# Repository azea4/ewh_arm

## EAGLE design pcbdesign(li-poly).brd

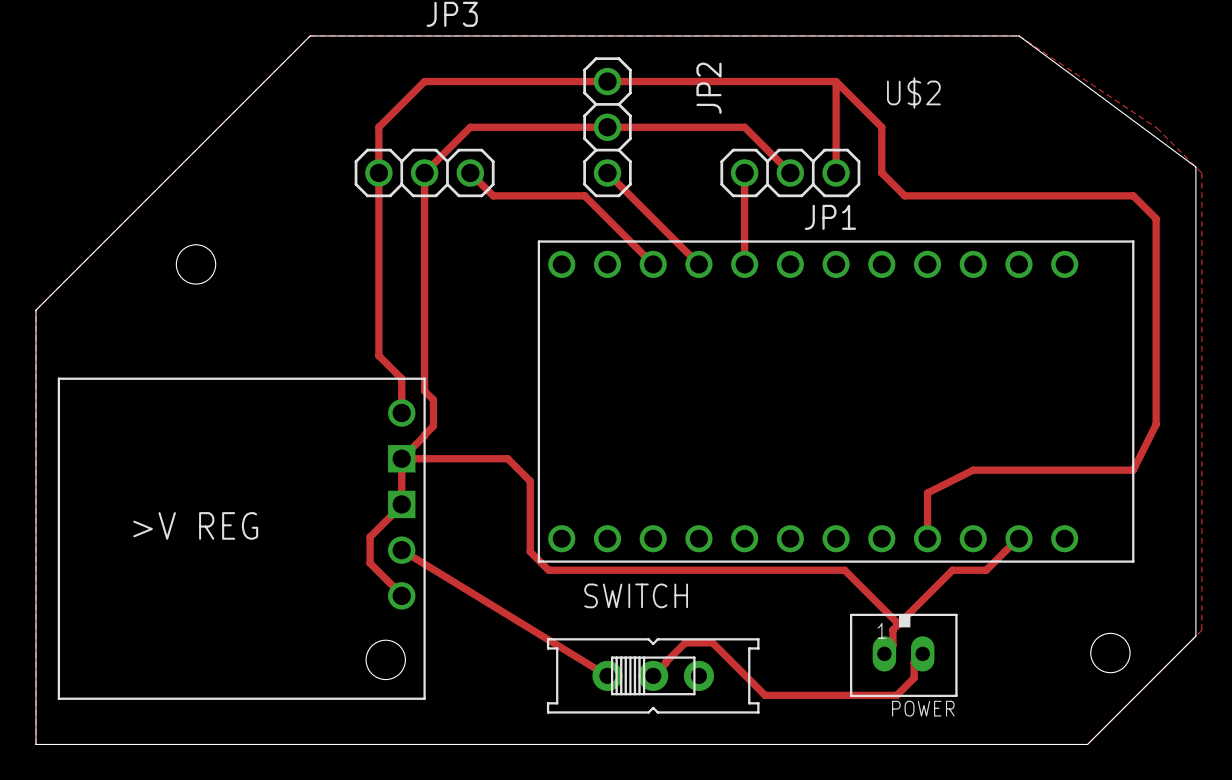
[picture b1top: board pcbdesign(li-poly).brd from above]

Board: 2 copper layers, 64.4 x 39.4 mm, 7 parts (0 on the bottom side), 7 nets.

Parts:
JP1, JP2, JP3: 1X03
POWER: JST-PH_2-PIN_HEADER; JST_B2B-PH_HEADER
SWITCH: EG1218
U$1: 5ASTEP-DOWNVOLTAGEREGULATOR; REG15D
U$2: ARDUINO_PROMICRO

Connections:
7.4V: POWER.P2, SWITCH.P
GND: JP1.2, JP2.2, JP3.2, POWER.P1, U$1.EN, U$1.GND, U$1.GND1, U$2.GND2
unnamed: JP1.3, U$2.5
unnamed: JP2.3, U$2.6
unnamed: JP3.3, U$2.7
unnamed: SWITCH.O, U$1.VIN
VCC: JP1.1, JP2.1, JP3.1, U$1.VOUT, U$2.VCC

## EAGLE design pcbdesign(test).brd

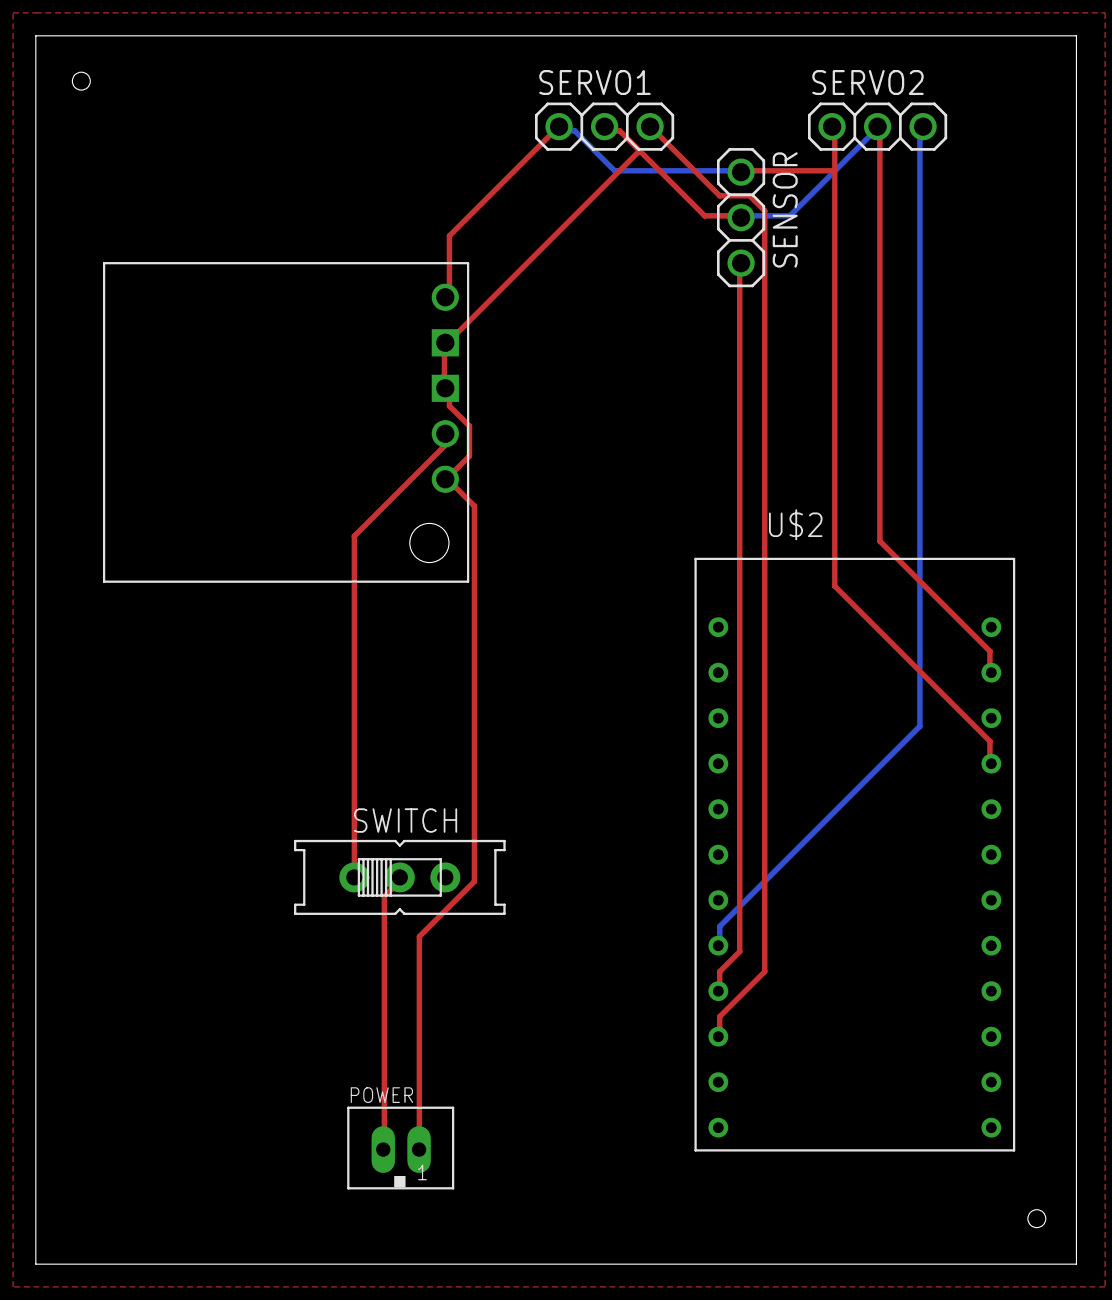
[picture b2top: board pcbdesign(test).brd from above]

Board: 2 copper layers, 58.1 x 68.6 mm, 7 parts (0 on the bottom side), 7 nets.

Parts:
POWER: JST-PH_2-PIN_HEADER; JST_B2B-PH_HEADER
SENSOR: 1X03
SERVO1, SERVO2: 1X03
SWITCH: EG1218
U$2: ARDUINO_PROMICRO
V_REGULATOR: 5ASTEP-DOWNVOLTAGEREGULATOR; REG15D

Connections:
7.4V: POWER.P2, SWITCH.P
GND: POWER.P1, SENSOR.2, SERVO1.2, SERVO2.2, U$2.GND2, V_REGULATOR.EN, V_REGULATOR.GND, V_REGULATOR.GND1
unnamed: SERVO2.3, U$2.5
unnamed: SENSOR.3, U$2.6
unnamed: SERVO1.3, U$2.7
unnamed: SWITCH.O, V_REGULATOR.VIN
VCC: SENSOR.1, SERVO1.1, SERVO2.1, U$2.VCC, V_REGULATOR.VOUT
